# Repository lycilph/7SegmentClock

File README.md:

# Mechanical Clock Project

## Overview
This repository contains the code, schematics, and documentation for building a custom mechanical clock using four digit modules in a 24-hour format. Each digit is driven by a stepper motor for mechanical display, controlled via an ESP32-S3 Super Mini master module over I2C. The project includes homing functionality with Hall effect sensors and LED indicators for status.

The setup is modular, with two digit modules on each side of the master (e.g., left2 ← left1 ← master → right1 → right2). Power is supplied externally at 5V, and modules are connected using JST XH connectors.

**Key Features:**
- 24-hour time display with mechanical digits.
- Stepper motor control for each digit.
- Automatic homing using Hall sensors.
- I2C communication with voltage level shifting for safety.
- Modular design for easy assembly and expansion.

## Components
### Master Module
- ESP32-S3 Super Mini (controls I2C bus and logic).

### Per Digit Module (x4)
- PCF8575 GPIO expander (I2C to GPIO).
- ULN2003 driver board (for stepper control).
- 28BYJ-48 stepper motor (drives the digit mechanism).
- A3144 Hall effect sensor (for homing).
- Red LED (homing in progress indicator).

### Additional Hardware
- External 5V power supply (2A+ recommended).
- Bidirectional I2C level shifter (e.g., BSS138-based, 4-channel) – **critical** to bridge 3.3V (ESP32) and 5V (PCF8575).
- Resistors: 4.7kΩ (I2C pull-ups x4), 10kΩ (A3144 pull-up x4), 330Ω (LED current limiter x4).
- Capacitors: 0.1µF ceramic (decoupling for each IC), 10-100µF electrolytic (at power entry).
- Wires: 20-22 AWG for power/GND; twisted-pair for SDA/SCL.
- Connectors: JST XH 4-pin (5V, GND, SDA, SCL).

## Usage
- Power the system; ESP32 boots and initializes modules.
- Clock syncs via NTP (add WiFi code if desired) or manual set.
- Homing: On startup, each digit homes using Hall sensor; LED blinks during process.
- Display updates every minute via steppers.
---

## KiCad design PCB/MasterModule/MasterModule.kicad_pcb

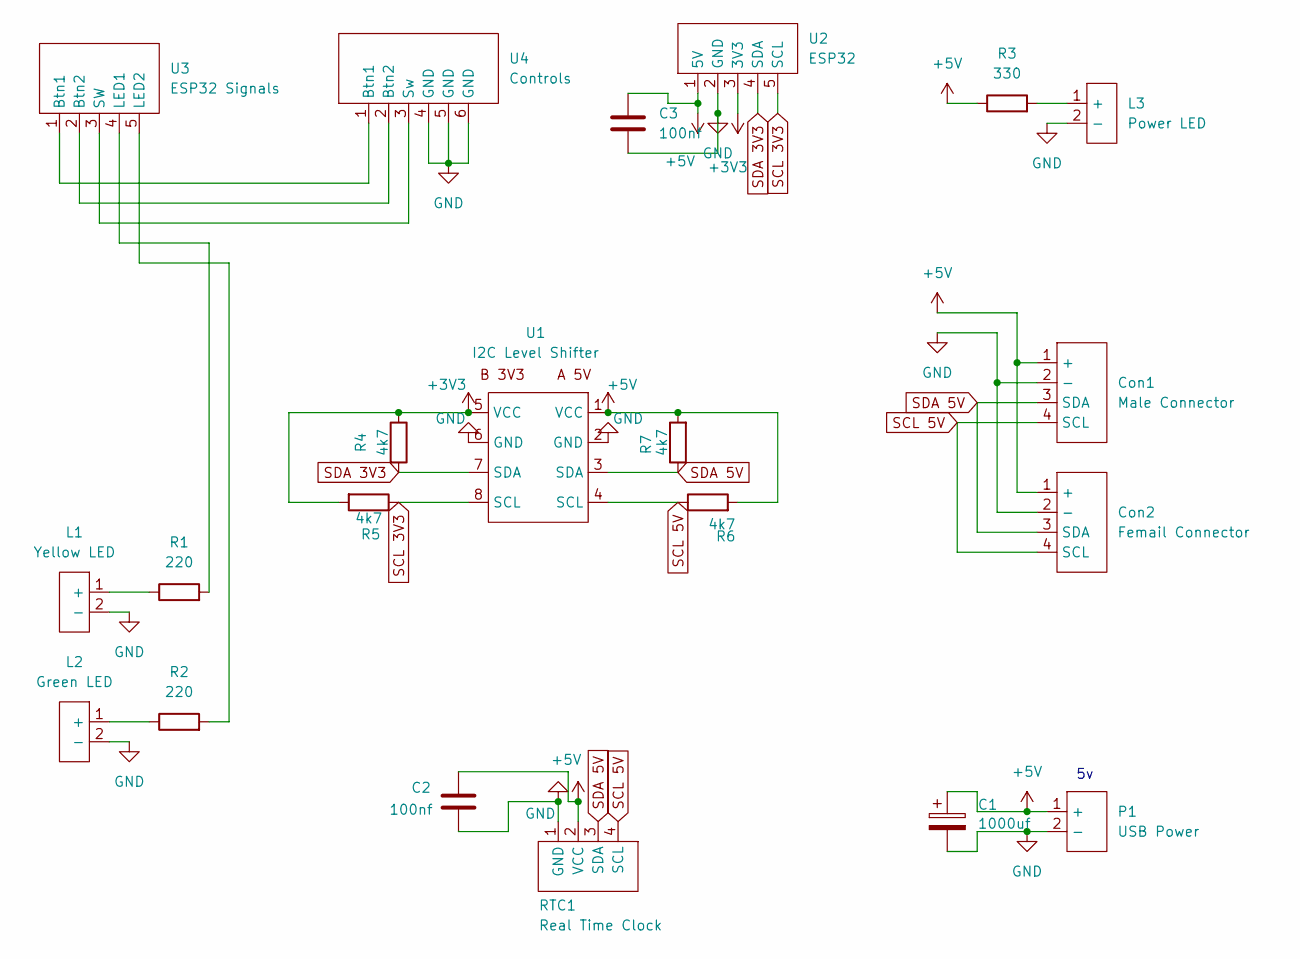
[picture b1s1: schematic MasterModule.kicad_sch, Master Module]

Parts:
C1: 1000uf; C_Radial_D8.0mm_H11.5mm_P3.50mm
C2, C3: 100nf; C_Disc_D3.0mm_W2.0mm_P2.50mm
Con1: Male Connector; JST_Connector_Footprint
Con2: Femail Connector; JST_Connector_Footprint
L1: Yellow LED; PinHeader_1x02_P2.54mm_Vertical
L2: Green LED; PinHeader_1x02_P2.54mm_Vertical
L3: Power LED; PinHeader_1x02_P2.54mm_Vertical
P1: USB Power; Power_Connection_Footprint
R1, R2: 220; R_Axial_DIN0204_L3.6mm_D1.6mm_P7.62mm_Horizontal
R3: 330; R_Axial_DIN0204_L3.6mm_D1.6mm_P7.62mm_Horizontal
R4, R5, R6, R7: 4k7; R_Axial_DIN0204_L3.6mm_D1.6mm_P7.62mm_Horizontal
RTC1: Real Time Clock; RTC_Module_Footprint
U1: I2C Level Shifter; I2C_Level_Shifter
U2: ESP32; PinHeader_1x05_P2.54mm_Vertical
U3: ESP32 Signals; PinHeader_1x05_P2.54mm_Vertical
U4: Controls; PinHeader_1x06_P2.54mm_Vertical

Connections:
+3V3: R4.1, R5.2, U1.5 (VCC), U2.3 (3V3)
+5V: C1.1, C2.1, C3.1, Con1.1 (+), Con2.1 (+), P1.1 (+), R3.1, R6.2, R7.2, RTC1.2 (VCC), U1.1 (VCC), U2.1 (5V)
GND: C1.2, C2.2, C3.2, Con1.2 (-), Con2.2 (-), L1.2 (-), L2.2 (-), L3.2 (-), P1.2 (-), RTC1.1 (GND), U1.2 (GND), U1.6 (GND), U2.2 (GND), U4.4 (GND), U4.5 (GND), U4.6 (GND)
unnamed: L1.1 (+), R1.1
unnamed: L2.1 (+), R2.1
unnamed: L3.1 (+), R3.2
unnamed: U3.1 (Btn1), U4.1 (Btn1)
unnamed: U3.2 (Btn2), U4.2 (Btn2)
unnamed: R1.2, U3.4 (LED1)
unnamed: R2.2, U3.5 (LED2)
unnamed: U3.3 (SW), U4.3 (Sw)
SCL 3V3: R5.1, U1.8 (SCL), U2.5 (SCL)
SCL 5V: Con1.4 (SCL), Con2.4 (SCL), R6.1, RTC1.4 (SCL), U1.4 (SCL)
SDA 3V3: R4.2, U1.7 (SDA), U2.4 (SDA)
SDA 5V: Con1.3 (SDA), Con2.3 (SDA), R7.1, RTC1.3 (SDA), U1.3 (SDA)

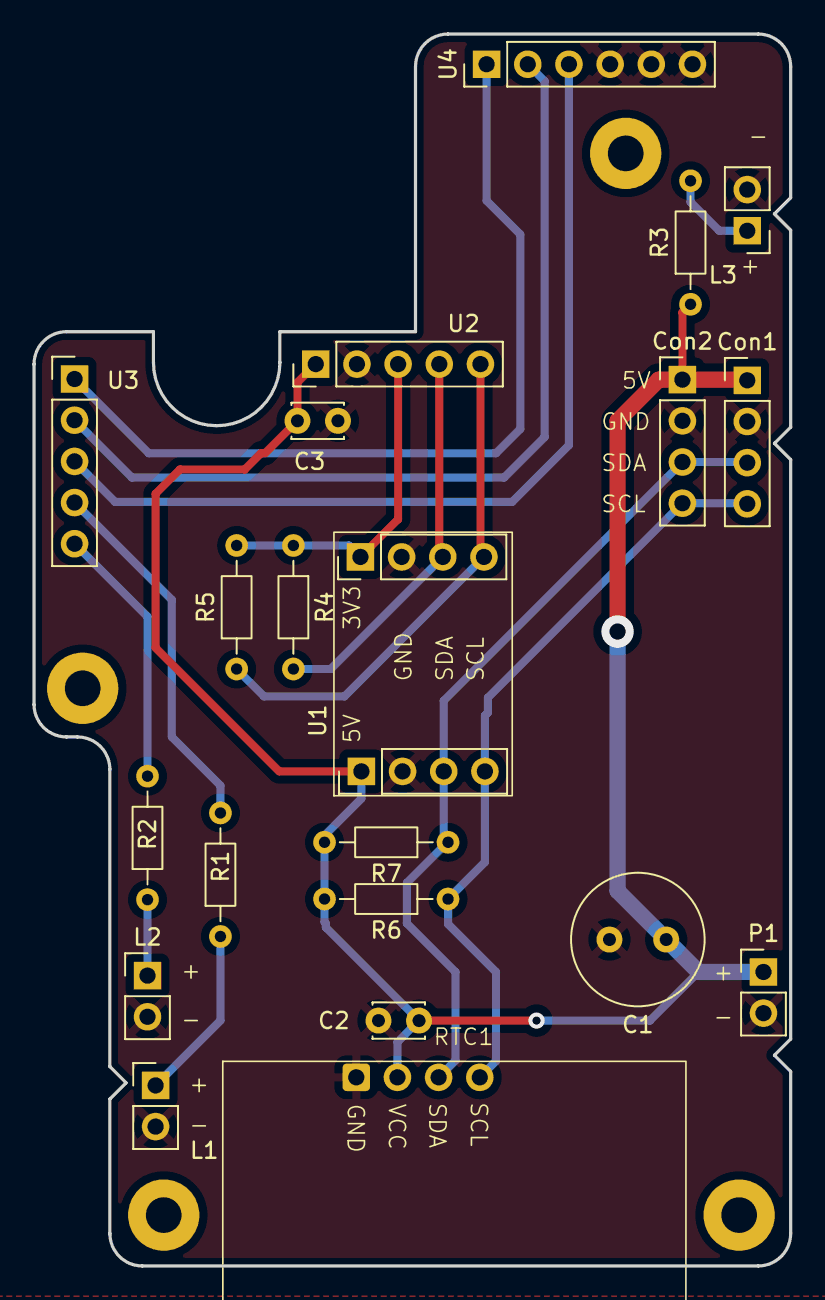
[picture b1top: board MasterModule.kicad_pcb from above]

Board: 2 copper layers, 46.7 x 76.0 mm, 21 parts (0 on the bottom side), 15 nets.

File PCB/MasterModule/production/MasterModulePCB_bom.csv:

Designator,Footprint,Quantity,Value,LCSC Part #
C1,C_Radial_D8.0mm_H11.5mm_P3.50mm,1,1000uf,
"C2, C3",C_Disc_D3.0mm_W2.0mm_P2.50mm,2,100nf,
CON1,JST_Connector_Footprint,1,Male Connector,
CON2,JST_Connector_Footprint,1,Femail Connector,
L1,PinHeader_1x02_P2.54mm_Vertical,1,Yellow LED,
L2,PinHeader_1x02_P2.54mm_Vertical,1,Green LED,
L3,PinHeader_1x02_P2.54mm_Vertical,1,Power LED,
P1,Power_Connection_Footprint,1,USB Power,
"R1, R2",R_Axial_DIN0204_L3.6mm_D1.6mm_P7.62mm_Horizontal,2,220,
R3,R_Axial_DIN0204_L3.6mm_D1.6mm_P7.62mm_Horizontal,1,330,
"R4, R5, R6, R7",R_Axial_DIN0204_L3.6mm_D1.6mm_P7.62mm_Horizontal,4,4k7,
RTC1,RTC_Module_Footprint,1,Real Time Clock,
U1,I2C_Level_Shifter,1,I2C Level Shifter,
U2,PinHeader_1x05_P2.54mm_Vertical,1,ESP32,
U3,PinHeader_1x05_P2.54mm_Vertical,1,ESP32 Signals,
U4,PinHeader_1x06_P2.54mm_Vertical,1,Controls,

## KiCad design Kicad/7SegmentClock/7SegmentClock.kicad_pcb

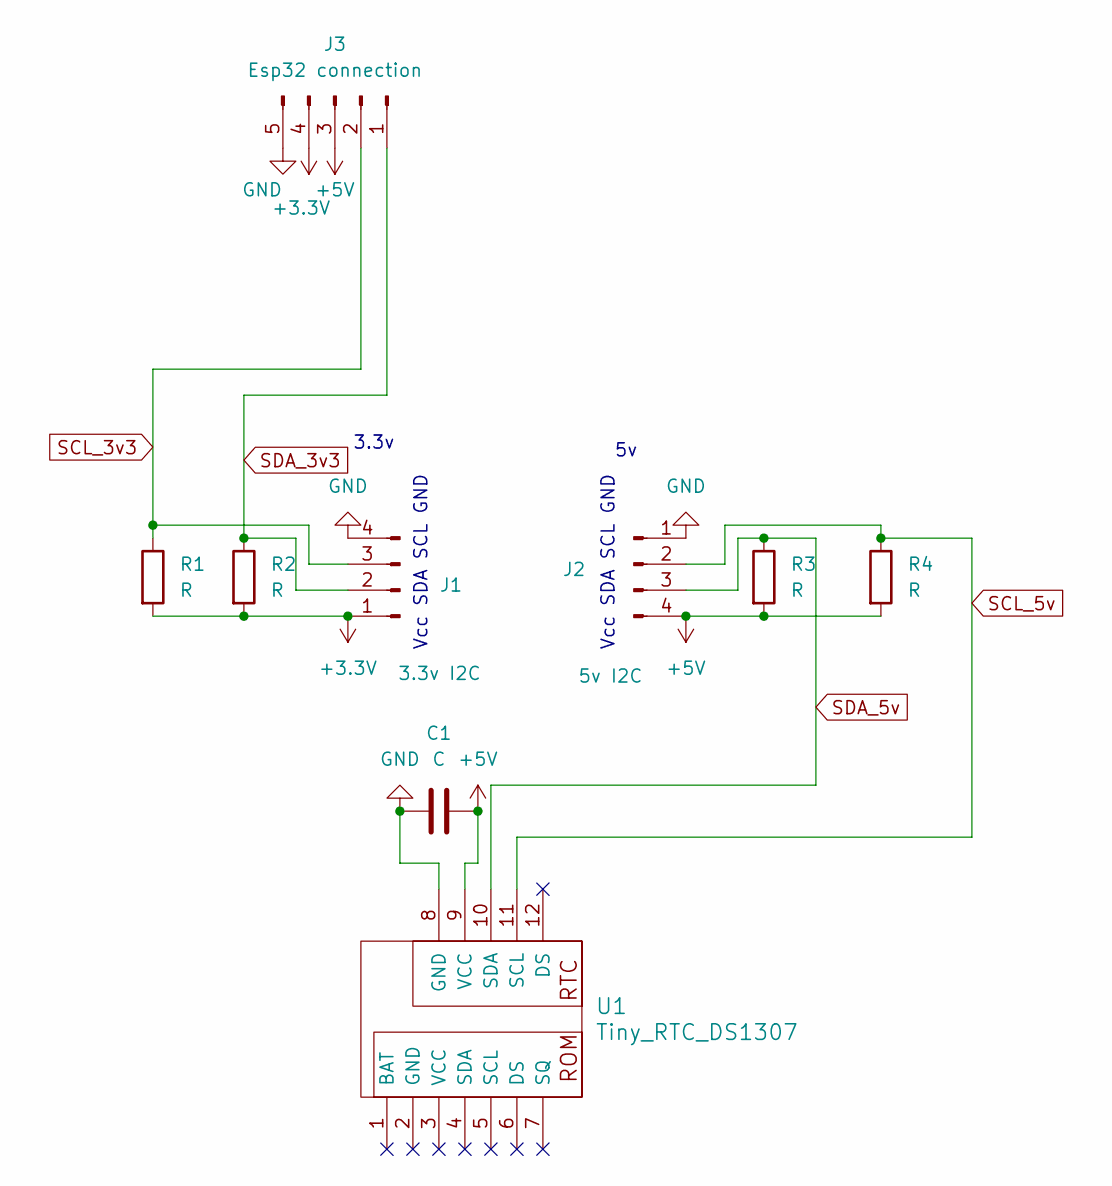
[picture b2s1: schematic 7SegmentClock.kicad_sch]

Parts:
C1: C; C_Disc_D3.0mm_W1.6mm_P2.50mm
J1: 3.3v I2C; PinHeader_1x04_P2.54mm_Vertical
J2: 5v I2C; PinHeader_1x04_P2.54mm_Vertical
J3: Esp32 connection; PinHeader_1x05_P2.54mm_Vertical
R1, R2, R3, R4: R; R_Axial_DIN0204_L3.6mm_D1.6mm_P5.08mm_Horizontal
U1: Tiny_RTC_DS1307

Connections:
+3.3V: J1.1, J3.4, R1.2, R2.2
+5V: C1.2, J2.4, J3.3, R3.2, R4.2, U1.9 (VCC)
GND: C1.1, J1.4, J2.1, J3.5, U1.8 (GND)
unnamed: J1.2, J3.1, R2.1
unnamed: J1.3, J3.2, R1.1
unnamed: J2.2, R4.1, U1.11 (SCL)
unnamed: J2.3, R3.1, U1.10 (SDA)

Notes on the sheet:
3.3v
Vcc SDA SCL GND

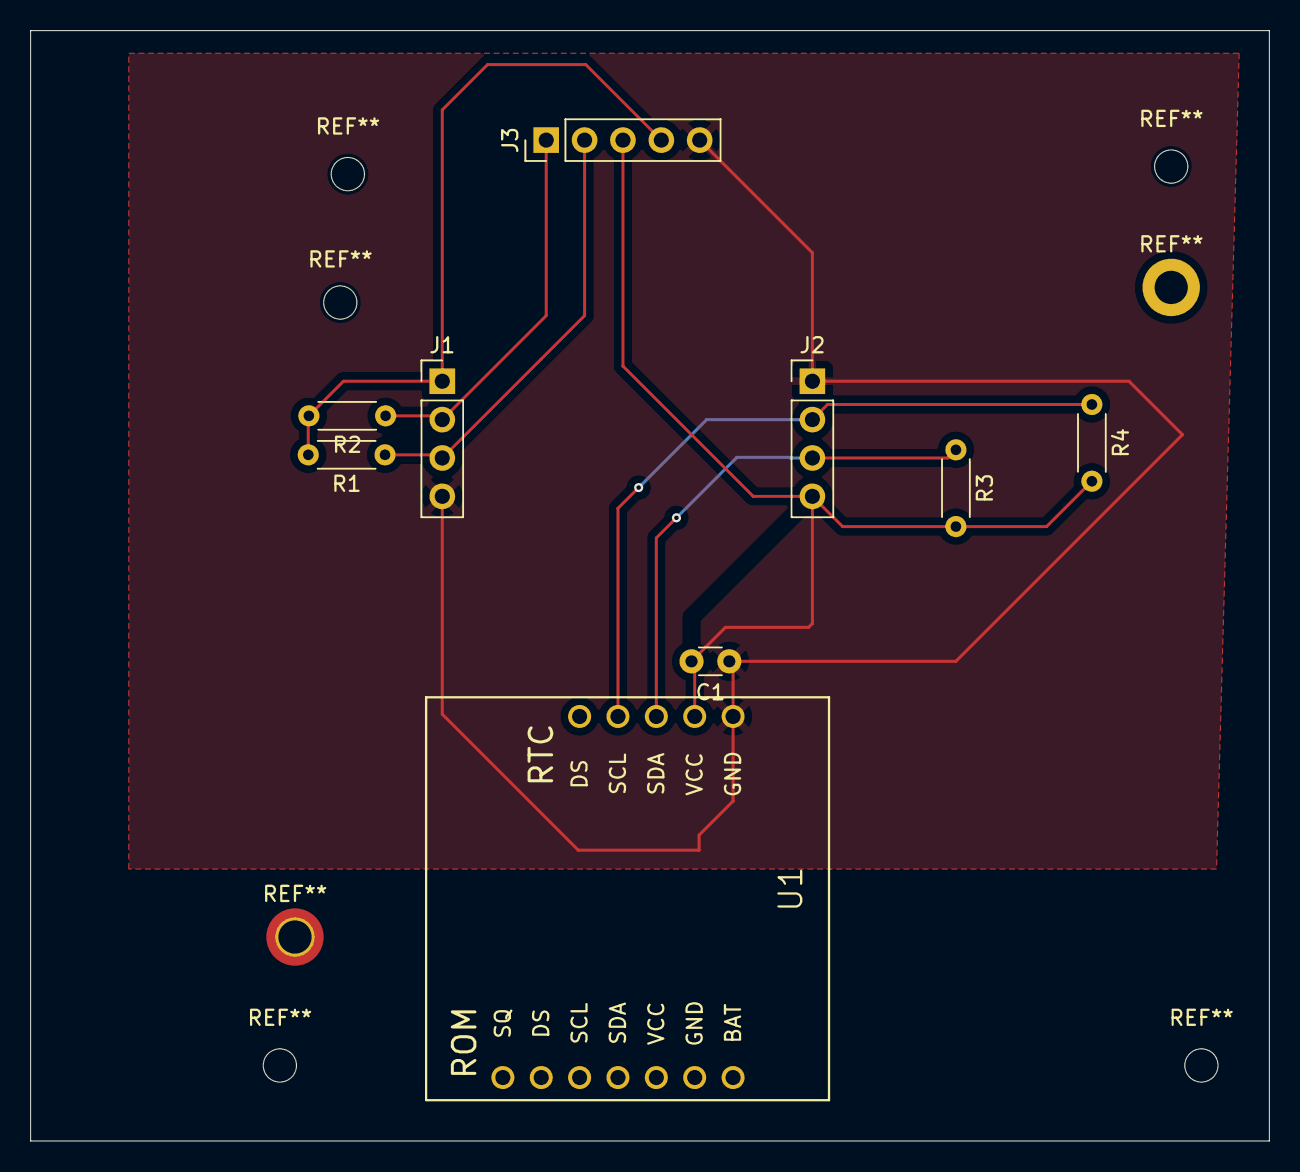
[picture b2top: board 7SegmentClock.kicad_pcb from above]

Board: 2 copper layers, 82.0 x 73.5 mm, 9 parts (0 on the bottom side), 7 nets.

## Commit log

2025-09-04 Backup of cad files
    Backup of cad files
2025-09-05 adding cad models
    adding cad models
2025-09-12 Main Cad models
2025-09-14 Adding arduino tests
2025-09-19 Added CAD models
2025-10-01 Add cad files and arduino sketch
    Added cad files for the DS1307 RTC module
    Added a sketch for the PCA9306 level shifter
2025-10-28 Working on master module PCB
2025-10-28 PCB update
2025-11-23 Added hall sensor and led to digit module
2025-12-03 Add a debug setup
2025-12-04 Created (and ordered) the pcb
